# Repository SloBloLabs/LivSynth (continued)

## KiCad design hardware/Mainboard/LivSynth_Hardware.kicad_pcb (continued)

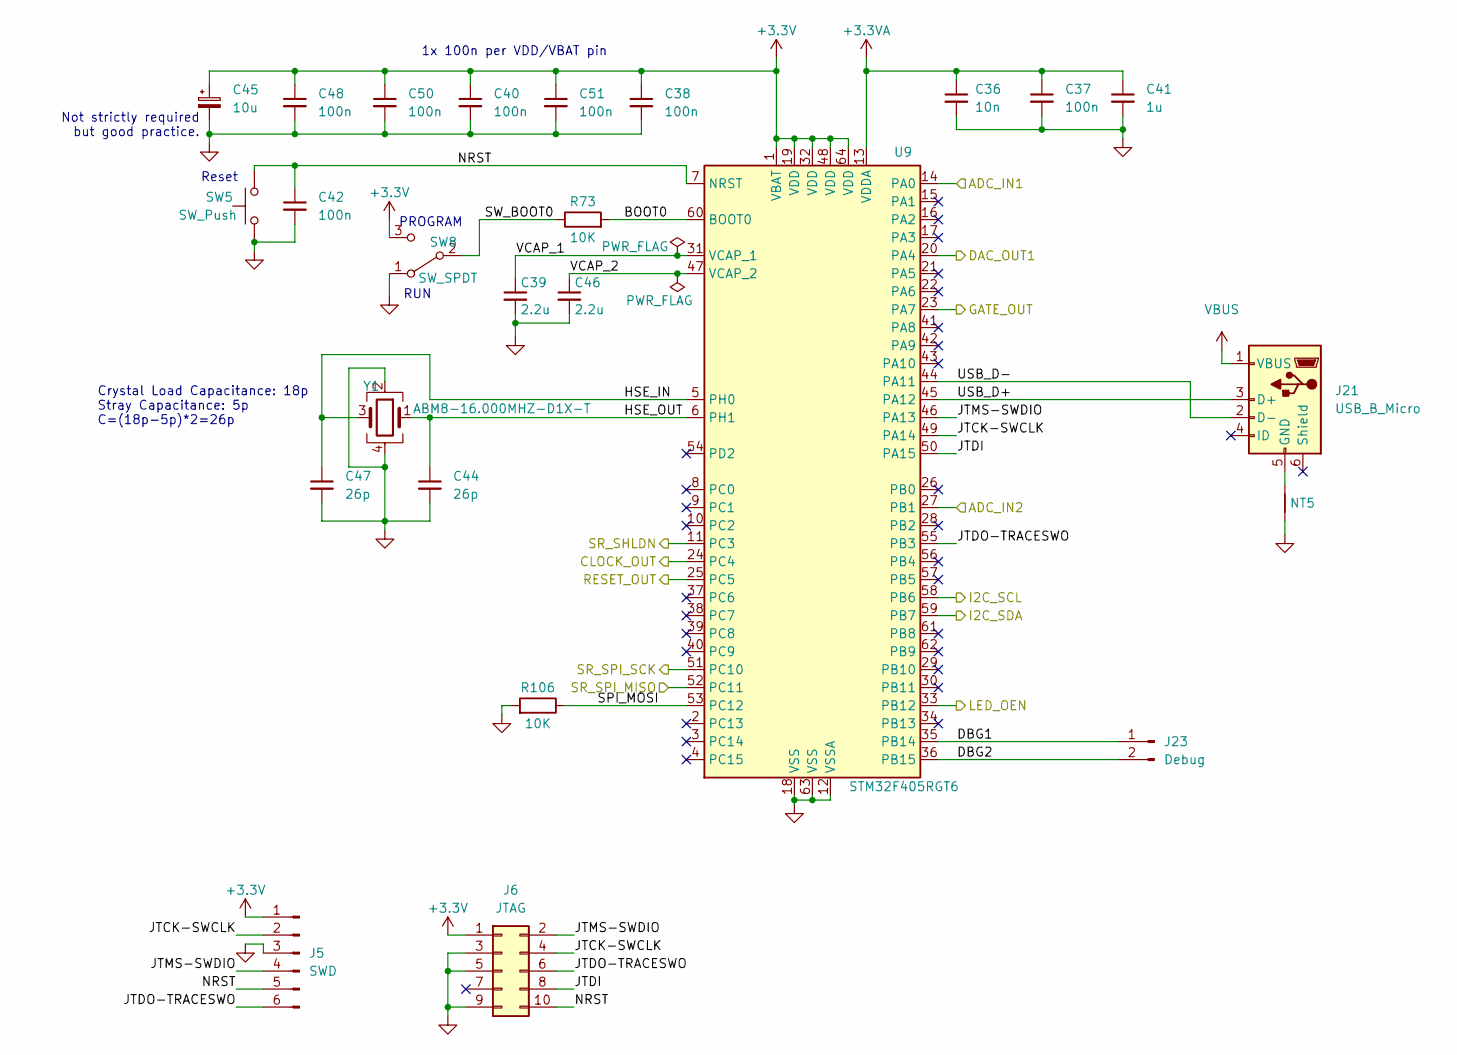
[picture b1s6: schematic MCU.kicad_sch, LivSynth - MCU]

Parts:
C36: 10n; C_Rect_L7.2mm_W2.5mm_P5.00mm_FKS2_FKP2_MKS2_MKP2
C37: 100n; C_Rect_L7.2mm_W2.5mm_P5.00mm_FKS2_FKP2_MKS2_MKP2
C38, C40, C42, C48, C50, C51: 100n; C_0603_1608Metric_Pad1.08x0.95mm_HandSolder; LCSC C282518
C39, C46: 2.2u; C_0603_1608Metric_Pad1.08x0.95mm_HandSolder; LCSC C268016
C41: 1u; C_Rect_L7.2mm_W5.5mm_P5.00mm_FKS2_FKP2_MKS2_MKP2
C44, C47: 26p; C_0603_1608Metric_Pad1.08x0.95mm_HandSolder; LCSC C519484
C45: 10u; CP_Radial_D8.0mm_P3.50mm
J5: SWD; PinHeader_1x06_P2.54mm_Vertical
J6: JTAG; PinHeader_2x05_P1.27mm_Vertical
J21: USB_B_Micro; USB_Micro-B_Wuerth_629105150521
J23: Debug; PinHeader_1x02_P2.54mm_Vertical
NT5: NetTie_2; NetTie-2_SMD_Pad0.5mm
R73, R106: 10K; R_Axial_DIN0207_L6.3mm_D2.5mm_P7.62mm_Horizontal
SW5: SW_Push; SW_SPST_EVQQ2
SW8: SW_SPDT; SW_E-Switch_EG1224_SPDT_Angled
U9: STM32F405RGT6; LQFP-64_10x10mm_P0.5mm; LCSC C15742
Y1: ABM8-16.000MHZ-D1X-T; Crystal_SMD_3225-4Pin_3.2x2.5mm_HandSoldering; LCSC C1985300

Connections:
+3.3V: C38.1, C40.1, C45.1, C48.1, C50.1, C51.1, J5.1, J6.1, SW8.3 (C), U9.1 (VBAT), U9.19 (VDD), U9.32 (VDD), U9.48 (VDD), U9.64 (VDD); also elsewhere on the board
+3.3VA: C36.1, C37.1, C41.1, U9.13 (VDDA); also elsewhere on the board
/EG/GATE_OUT: U9.23 (PA7); also elsewhere on the board
/IO/ADC_IN1: U9.14 (PA0); also elsewhere on the board
/IO/ADC_IN2: U9.27 (PB1); also elsewhere on the board
/IO/CLOCK_OUT: U9.24 (PC4); also elsewhere on the board
/IO/I2C_SCL_IN: U9.58 (PB6); also elsewhere on the board
/IO/I2C_SDA_IN: U9.59 (PB7); also elsewhere on the board
/IO/LED_OEN: U9.33 (PB12); also elsewhere on the board
/IO/RESET_OUT: U9.25 (PC5); also elsewhere on the board
/IO/SR_SHLDN: U9.11 (PC3); also elsewhere on the board
/IO/SR_SPI_CLK: U9.51 (PC10); also elsewhere on the board
/IO/SR_SPI_MISO: U9.52 (PC11); also elsewhere on the board
/MCU/BOOT0: R73.2, U9.60 (BOOT0)
/MCU/DAC_OUT1: U9.20 (PA4); also elsewhere on the board
/MCU/DBG1: J23.1, U9.35 (PB14)
/MCU/DBG2: J23.2, U9.36 (PB15)
/MCU/HSE_IN: C47.1, U9.5 (PH0), Y1.3
/MCU/HSE_OUT: C44.1, U9.6 (PH1), Y1.1
/MCU/JTCK-SWCLK: J5.2, J6.4, U9.49 (PA14)
/MCU/JTDI: J6.8, U9.50 (PA15)
/MCU/JTDO-TRACESWO: J5.6, J6.6, U9.55 (PB3)
/MCU/JTMS-SWDIO: J5.4, J6.2, U9.46 (PA13)
/MCU/NRST: C42.1, J5.5, J6.10, SW5.2, U9.7 (NRST)
/MCU/SPI_MOSI: R106.1, U9.53 (PC12)
/MCU/SW_BOOT0: R73.1, SW8.2 (B)
/MCU/USB_D+: J21.3 (D+), U9.45 (PA12)
/MCU/USB_D-: J21.2 (D-), U9.44 (PA11)
/MCU/VCAP_1: C39.1, U9.31 (VCAP_1)
/MCU/VCAP_2: C46.1, U9.47 (VCAP_2)
GND: C36.2, C37.2, C38.2, C39.2, C40.2, C41.2, C42.2, C44.2, C45.2, C46.2, C47.2, C48.2, C50.2, C51.2, J5.3, J6.3, J6.5, J6.9, NT5.1, R106.2, SW5.1, SW8.1 (A), U9.12 (VSSA), U9.18 (VSS), U9.63 (VSS), Y1.2, Y1.4; also elsewhere on the board
unnamed: J21.5 (GND), NT5.2
VBUS: J21.1 (VBUS); also elsewhere on the board

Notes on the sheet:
Not strictly required but good practice.
RUN
Crystal Load Capacitance: 18p Stray Capacitance: 5p C=(18p-5p)*2=26p
PROGRAM
1x 100n per VDD/VBAT pin
Reset

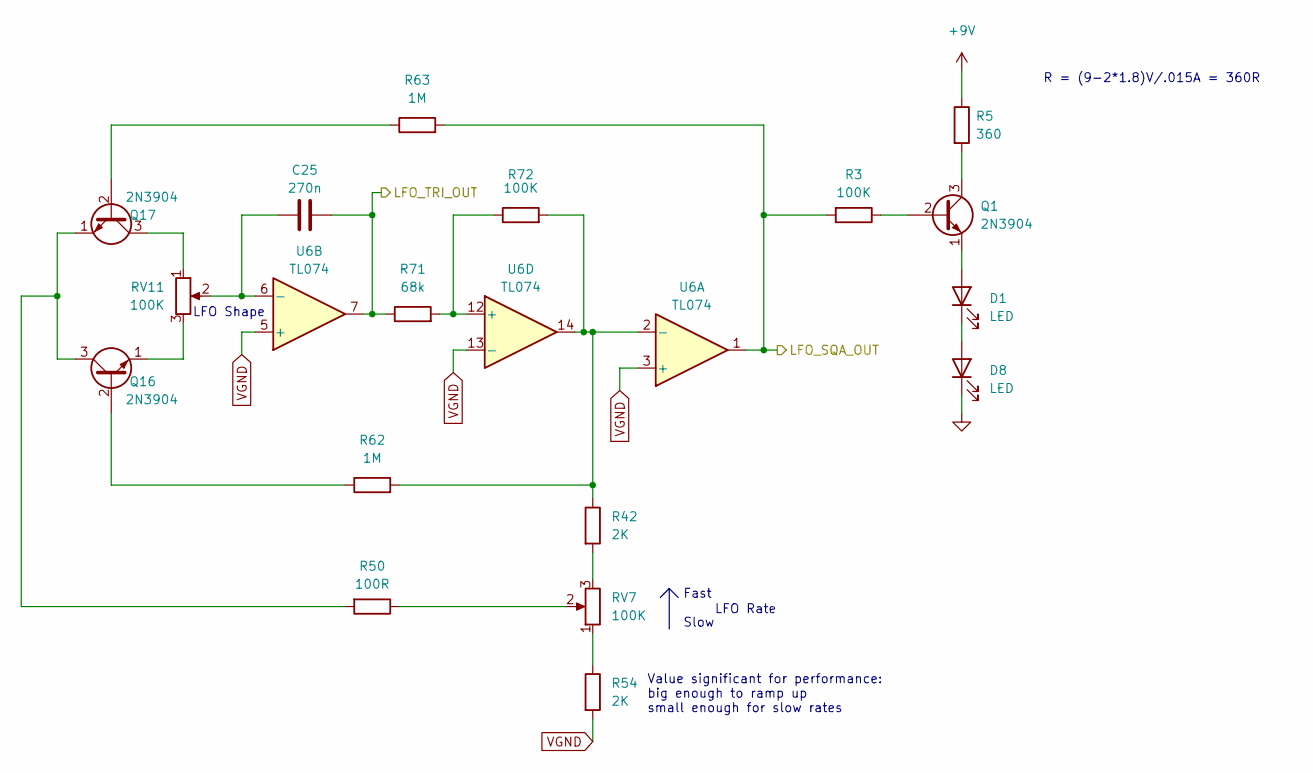
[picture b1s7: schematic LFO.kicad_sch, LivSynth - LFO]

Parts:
C25: 270n; C_Rect_L7.2mm_W5.5mm_P5.00mm_FKS2_FKP2_MKS2_MKP2
D1, D8: LED; LED_D5.0mm
Q1, Q16, Q17: 2N3904; TO-92_Inline
R3, R72: 100K; R_Axial_DIN0207_L6.3mm_D2.5mm_P7.62mm_Horizontal
R5: 360; R_Axial_DIN0207_L6.3mm_D2.5mm_P7.62mm_Horizontal
R42, R54: 2K; R_Axial_DIN0207_L6.3mm_D2.5mm_P7.62mm_Horizontal
R50: 100R; R_Axial_DIN0207_L6.3mm_D2.5mm_P7.62mm_Horizontal
R62, R63: 1M; R_Axial_DIN0207_L6.3mm_D2.5mm_P7.62mm_Horizontal
R71: 68k; R_Axial_DIN0207_L6.3mm_D2.5mm_P7.62mm_Horizontal
RV7, RV11: 100K; RV141F-40-20BL
U6: TL074; SOIC-14_3.9x8.7mm_P1.27mm; LCSC C2057504

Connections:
+9V: R5.1; also elsewhere on the board
/LFO/LFO_SQA_OUT: R3.2, R63.2, U6.1; also elsewhere on the board
/LFO/LFO_TRI_OUT: C25.2, R71.1, U6.7; also elsewhere on the board
GND: D8.1 (K); also elsewhere on the board
unnamed: D1.2 (A), Q1.1 (E)
unnamed: D1.1 (K), D8.2 (A)
unnamed: Q1.2 (B), R3.1
unnamed: Q1.3 (C), R5.2
unnamed: Q16.2 (B), R62.1
unnamed: Q16.3 (C), Q17.1 (E), R50.2
unnamed: Q16.1 (E), RV11.3
unnamed: Q17.2 (B), R63.1
unnamed: Q17.3 (C), RV11.1
unnamed: R42.2, RV7.3
unnamed: R50.1, RV7.2
unnamed: R54.1, RV7.1
unnamed 191: U6.8; also elsewhere on the board
unnamed: R42.1, R62.2, R72.2, U6.2 (-), U6.14
unnamed: C25.1, RV11.2, U6.6 (-)
unnamed 245: U6.10 (+); also elsewhere on the board
unnamed 246: U6.9 (-); also elsewhere on the board
unnamed: R71.2, R72.1, U6.12 (+)
VGND: R54.2, U6.3 (+), U6.5 (+), U6.13 (-); also elsewhere on the board

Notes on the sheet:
LFO Shape
LFO Rate
Fast Slow
R = (9-2*1.8)V/.015A = 360R
Value significant for performance: big enough to ramp up small enough for slow rates

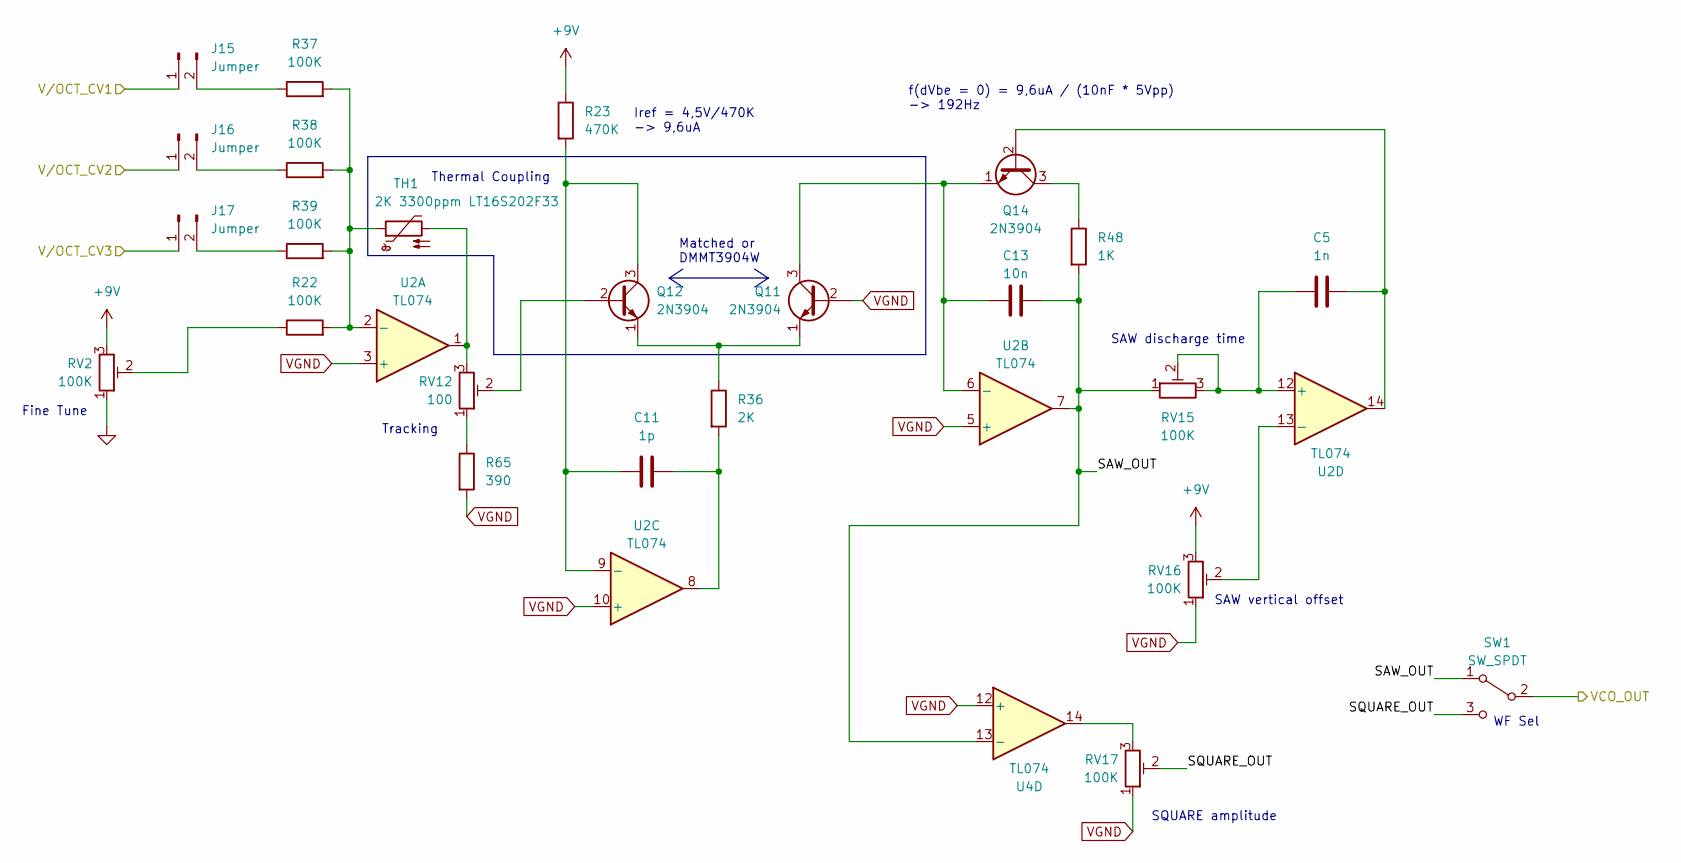
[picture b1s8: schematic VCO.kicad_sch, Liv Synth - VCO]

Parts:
C5: 1n; C_Rect_L7.2mm_W2.5mm_P5.00mm_FKS2_FKP2_MKS2_MKP2
C11: 1p; C_Disc_D3.0mm_W1.6mm_P2.50mm
C13: 10n; C_Rect_L7.2mm_W2.5mm_P5.00mm_FKS2_FKP2_MKS2_MKP2
J15, J16, J17: Jumper; PinHeader_1x02_P2.54mm_Vertical
Q11, Q12, Q14: 2N3904; TO-92_Inline
R22, R37, R38, R39: 100K; R_Axial_DIN0207_L6.3mm_D2.5mm_P7.62mm_Horizontal
R23: 470K; R_Axial_DIN0207_L6.3mm_D2.5mm_P7.62mm_Horizontal
R36: 2K; R_Axial_DIN0207_L6.3mm_D2.5mm_P7.62mm_Horizontal
R48: 1K; R_Axial_DIN0207_L6.3mm_D2.5mm_P7.62mm_Horizontal
R65: 390; R_Axial_DIN0207_L6.3mm_D2.5mm_P7.62mm_Horizontal
RV2, RV15, RV16, RV17: 100K; Potentiometer_Bourns_3296W_Vertical
RV12: 100; Potentiometer_Bourns_3296W_Vertical
SW1: SW_SPDT; SW_Toggle_MS500
TH1: 2K 3300ppm LT16S202F33; R_Axial_DIN0207_L6.3mm_D2.5mm_P7.62mm_Horizontal
U2, U4: TL074; SOIC-14_3.9x8.7mm_P1.27mm; LCSC C2057504

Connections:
+9V: R23.1, RV2.3, RV16.3; also elsewhere on the board
/ModMatrix/VCF_EG_OUT: U4.1; also elsewhere on the board
/ModMatrix/VCO_EG_OUT: J17.1, U4.7; also elsewhere on the board
/ModMatrix/VCO_LFO_OUT: J16.1; also elsewhere on the board
/Slew/V/OCT_OUT: J15.1, U4.8, U4.9 (-)
/VCF/VCF_IN: SW1.2 (B); also elsewhere on the board
/VCO/SAW_OUT: C13.2, R48.2, RV15.1, SW1.1 (A), U2.7, U4.13 (-)
/VCO/SQUARE_OUT: RV17.2, SW1.3 (C)
GND: RV2.1; also elsewhere on the board
unnamed: C11.2, R36.2, U2.8
unnamed: J15.2, R37.1
unnamed: J16.2, R38.1
unnamed: J17.2, R39.1
unnamed: C13.1, Q11.3 (C), Q14.1 (E), U2.6 (-)
unnamed: Q11.1 (E), Q12.1 (E), R36.1
unnamed: Q12.2 (B), RV12.2
unnamed: C11.1, Q12.3 (C), R23.2, U2.9 (-)
unnamed: C5.2, Q14.2 (B), U2.14
unnamed: Q14.3 (C), R48.1
unnamed: R22.1, RV2.2
unnamed: R65.1, RV12.1
unnamed: RV12.3, TH1.2, U2.1
unnamed: RV17.3, U4.14
unnamed: R22.2, R37.2, R38.2, R39.2, TH1.1, U2.2 (-)
unnamed: C5.1, RV15.2, RV15.3, U2.12 (+)
unnamed: RV16.2, U2.13 (-)
unnamed 235: U4.3 (+); also elsewhere on the board
unnamed 236: U4.2 (-); also elsewhere on the board
unnamed 237: U4.5 (+); also elsewhere on the board
unnamed 238: U4.6 (-); also elsewhere on the board
unnamed 239: U4.10 (+); also elsewhere on the board
VGND: Q11.2 (B), R65.2, RV16.1, RV17.1, U2.3 (+), U2.5 (+), U2.10 (+), U4.12 (+); also elsewhere on the board

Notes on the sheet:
f(dVbe = 0) = 9,6uA / (10nF * 5Vpp) -> 192Hz
WF Sel
SAW discharge time
Iref = 4,5V/470K -> 9,6uA
Tracking
Matched or DMMT3904W
SQUARE amplitude
Thermal Coupling
Fine Tune
SAW vertical offset

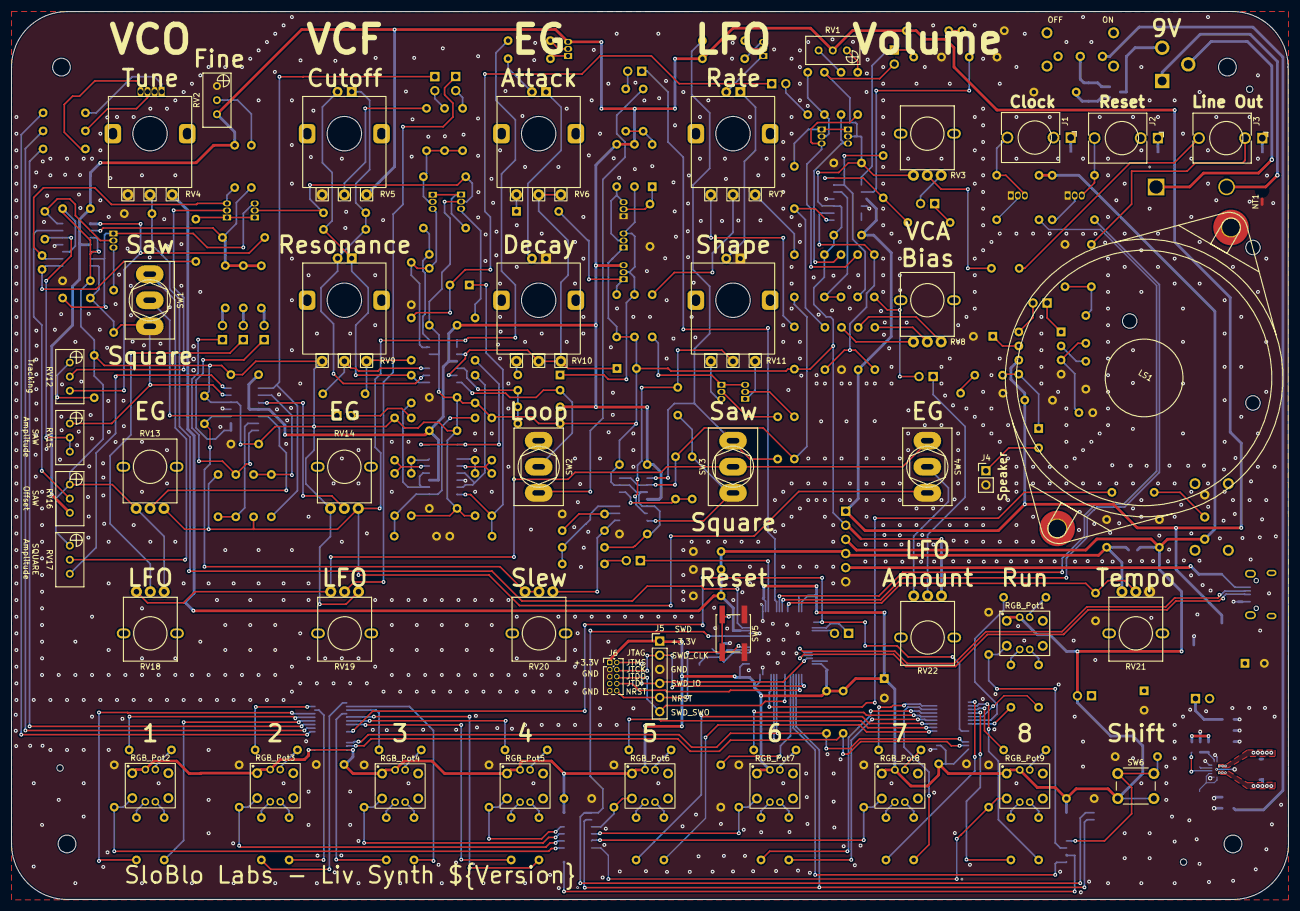
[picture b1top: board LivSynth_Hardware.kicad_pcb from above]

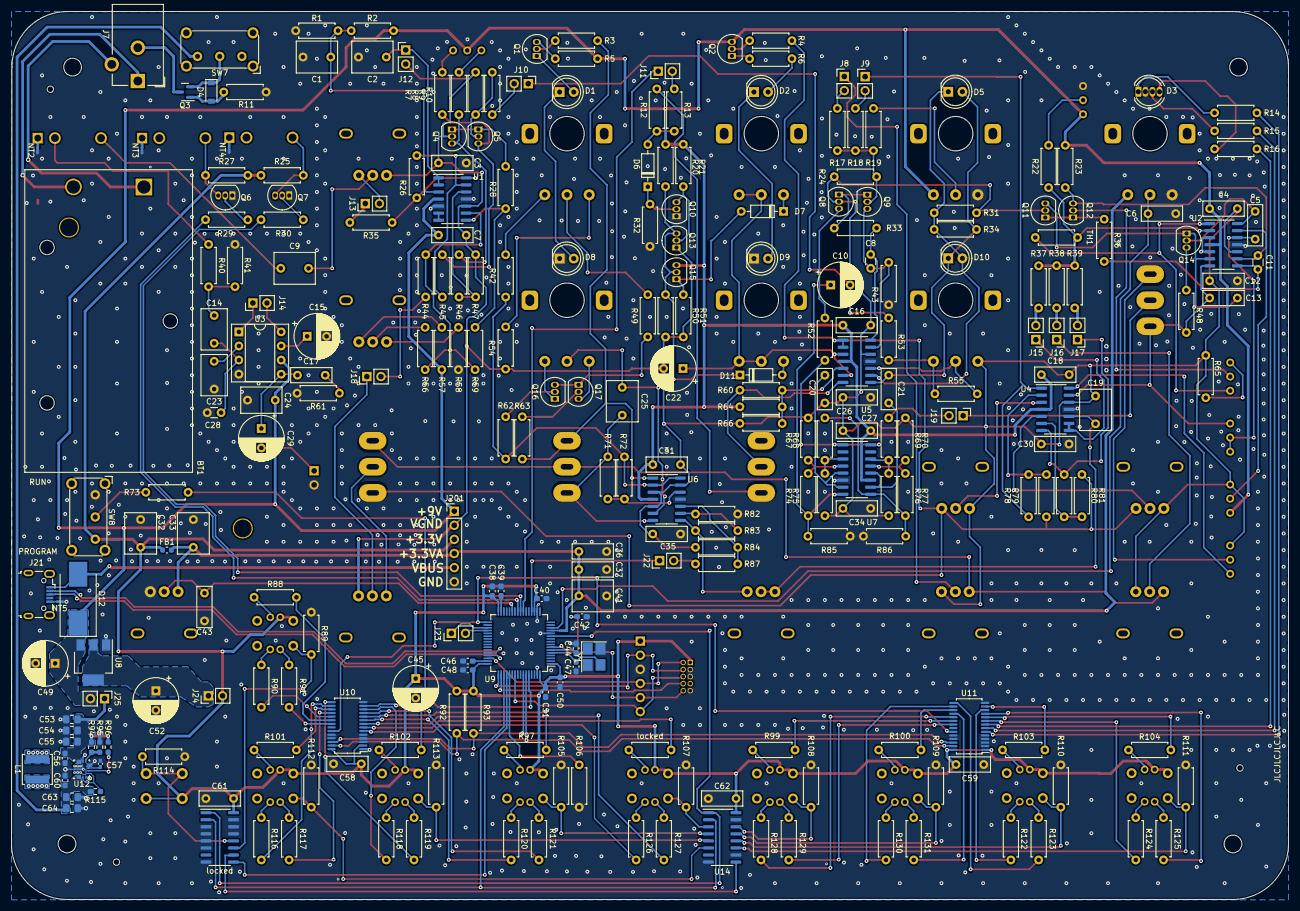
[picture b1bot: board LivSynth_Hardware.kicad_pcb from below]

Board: 2 copper layers, 230.0 x 159.9 mm, 320 parts (268 on the bottom side), 254 nets.

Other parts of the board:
C19: 1u; C_Rect_L7.2mm_W5.5mm_P5.00mm_FKS2_FKP2_MKS2_MKP2
J10, J18, J22: Jumper; PinHeader_1x02_P2.54mm_Vertical
Q4, Q5: 2N3904; TO-92_Inline
R7, R9: 20K; R_Axial_DIN0207_L6.3mm_D2.5mm_P7.62mm_Horizontal
R8: 390; R_Axial_DIN0207_L6.3mm_D2.5mm_P7.62mm_Horizontal
R10, R26, R47, R56, R78, R79, R80, R81, R82, R83, R87: 100K; R_Axial_DIN0207_L6.3mm_D2.5mm_P7.62mm_Horizontal
R28: 4K7; R_Axial_DIN0207_L6.3mm_D2.5mm_P7.62mm_Horizontal
R35, R45, R46: 1K; R_Axial_DIN0207_L6.3mm_D2.5mm_P7.62mm_Horizontal
R44: 68K; R_Axial_DIN0207_L6.3mm_D2.5mm_P7.62mm_Horizontal
R57: 24K; R_Axial_DIN0207_L6.3mm_D2.5mm_P7.62mm_Horizontal
R58: 150K; R_Axial_DIN0207_L6.3mm_D2.5mm_P7.62mm_Horizontal
R59: 47K; R_Axial_DIN0207_L6.3mm_D2.5mm_P7.62mm_Horizontal
R84: 330K; R_Axial_DIN0207_L6.3mm_D2.5mm_P7.62mm_Horizontal
RV1: 1K; Potentiometer_Bourns_3296W_Vertical
RV8, RV13, RV14, RV18, RV19, RV20, RV22: 100K; Alpha_RD901F
SW3, SW4: SW_SPDT; SW_Toggle_MS500
locked: 220; R_Axial_DIN0207_L6.3mm_D2.5mm_P7.62mm_Horizontal
locked#2: 74HC165; SOIC-16_3.9x9.9mm_P1.27mm

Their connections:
+3.3V: locked#2.16 (VCC); also elsewhere on the board
+9V: R57.1, RV1.2; also elsewhere on the board
/EG/AR_OUT: R79.1, R81.1, RV13.3, RV14.3, SW4.1 (A); also elsewhere on the board
/IO/BTN9: locked#2.11 (D0); also elsewhere on the board
/IO/BTN_SHIFT: locked#2.12 (D1); also elsewhere on the board
/IO/P5_G: locked.2; also elsewhere on the board
/IO/SR_SHLDN: locked#2.1 (~PL); also elsewhere on the board
/IO/SR_SPI_CLK: locked#2.2 (CP); also elsewhere on the board
/IO/SR_SPI_MISO: locked#2.9 (Q7); also elsewhere on the board
/IO/VCA_IN: R35.2; also elsewhere on the board
/LFO/LFO_SQA_OUT: SW3.1 (A); also elsewhere on the board
/LFO/LFO_TRI_OUT: SW3.3 (C); also elsewhere on the board
/MCU/DAC_OUT1: J22.1; also elsewhere on the board
/ModMatrix/VCA_CV_OUT: J18.1, RV22.2
/ModMatrix/VCF_EG_OUT: R78.2; also elsewhere on the board
/ModMatrix/VCF_LFO_OUT: RV19.2; also elsewhere on the board
/ModMatrix/VCO_EG_OUT: R80.2; also elsewhere on the board
/ModMatrix/VCO_LFO_OUT: RV18.2; also elsewhere on the board
/VCA/VCA_IN: J10.1; also elsewhere on the board
GND: R58.2, R82.1, locked#2.3 (D4), locked#2.4 (D5), locked#2.5 (D6), locked#2.6 (D7), locked#2.8 (GND), locked#2.13 (D2), locked#2.14 (D3), locked#2.15 (~CE); also elsewhere on the board
unnamed: J10.2, R10.1
unnamed: J18.2, R44.1
unnamed: J22.2, R87.1
unnamed: Q4.2 (B), R8.1, R10.2
unnamed: Q4.3 (C), R7.2, R45.1
unnamed: Q4.1 (E), Q5.1 (E), R28.1
unnamed: Q5.3 (C), R9.2, R46.1
unnamed: R7.1, RV1.1
unnamed: R9.1, RV1.3
unnamed 179: R26.1, R35.1; also elsewhere on the board
unnamed 180: R28.2, R59.2; also elsewhere on the board
unnamed: R56.1, RV8.2
unnamed: R57.2, RV8.3
unnamed: R58.1, RV8.1
unnamed 191: R83.2, RV20.1; also elsewhere on the board
unnamed 208: locked.1; also elsewhere on the board
unnamed: RV18.3, RV19.3, SW3.2 (B), SW4.3 (C)
unnamed: RV22.3, SW4.2 (B)
unnamed 226: R44.2, R56.2, R59.1; also elsewhere on the board
unnamed 227: R46.2, R47.2; also elsewhere on the board
unnamed 228: R26.2, R45.2; also elsewhere on the board
unnamed 235: RV14.2; also elsewhere on the board
unnamed 236: R78.1, R79.2; also elsewhere on the board
unnamed 237: RV13.2; also elsewhere on the board
unnamed 238: R80.1, R81.2; also elsewhere on the board
unnamed 239: C19.1, RV20.2, RV20.3; also elsewhere on the board
unnamed 245: R84.2, R87.2; also elsewhere on the board
unnamed 246: R82.2, R83.1; also elsewhere on the board
unnamed 253: locked#2.10 (DS); also elsewhere on the board
VGND: C19.2, Q5.2 (B), R8.2, R47.1, R84.1, RV13.1, RV14.1, RV18.1, RV19.1, RV22.1; also elsewhere on the board

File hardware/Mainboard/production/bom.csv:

Designator,Footprint,Quantity,Value,LCSC Part #
BT1,BatteryHolder_Eagle_12BH611-GR,1,9V,
"C1, C19, C2, C25, C32, C33, C41, C9",C_Rect_L7.2mm_W5.5mm_P5.00mm_FKS2_FKP2_MKS2_MKP2,8,1u,
C10,CP_Radial_D8.0mm_P3.50mm,1,33u,
"C11, C8",C_Disc_D3.0mm_W1.6mm_P2.50mm,2,1p,
"C12, C13, C16, C17, C18, C26, C27, C3, C30, C31, C34, C35, C37, C4, C43, C58, C59, C6, C61, C62, C7",C_Rect_L7.2mm_W2.5mm_P5.00mm_FKS2_FKP2_MKS2_MKP2,21,100n,
"C14, C23, C24",C_Rect_L7.2mm_W4.5mm_P5.00mm_FKS2_FKP2_MKS2_MKP2,3,270n,
"C15, C22, C45, C49",CP_Radial_D8.0mm_P3.50mm,4,10u,
"C20, C5",C_Rect_L7.2mm_W2.5mm_P5.00mm_FKS2_FKP2_MKS2_MKP2,2,1n,
"C21, C36",C_Rect_L7.2mm_W2.5mm_P5.00mm_FKS2_FKP2_MKS2_MKP2,2,10n,
C28,C_Disc_D3.0mm_W1.6mm_P2.50mm,1,47p,
C29,CP_Radial_D8.0mm_P3.50mm,1,470u,
"C38, C40, C42, C48, C50, C51",C_0603_1608Metric_Pad1.08x0.95mm_HandSolder,6,100n,C282518
"C39, C46",C_0603_1608Metric_Pad1.08x0.95mm_HandSolder,2,2.2u,C268016
"C44, C47",C_0603_1608Metric_Pad1.08x0.95mm_HandSolder,2,26p,C519484
C52,CP_Radial_D8.0mm_P3.50mm,1,22u,
"C53, C54, C55",C_0805_2012Metric_Pad1.18x1.45mm_HandSolder,3,22u,C415296
"C56, C60",C_0603_1608Metric_Pad1.08x0.95mm_HandSolder,2,10u, C96446
C57,C_0402_1005Metric_Pad0.74x0.62mm_HandSolder,1,100n, C1523
"C63, C64",C_0805_2012Metric_Pad1.18x1.45mm_HandSolder,2,10u, C109040
"D1, D10, D2, D5, D8, D9",LED_D5.0mm,6,LED,
"D11, D6, D7",D_DO-35_SOD27_P7.62mm_Horizontal,3,1N4148,
D12,D_SMC_Handsoldering,1,SS310,
D3,LED_D5.0mm-4_RGB,1,LED_RKGB,
D4,D_SOD-123,1,8V2, C438308
FB1,L_0603_1608Metric,1,120R@100MHz,
"H1, H2, H5, H6",MountingHole_3.2mm_M3,4,MountingHole,
"J1, J2, J3",Thonkiconn_PJ398SM,3,PJ398SM,
"J10, J11, J13, J14, J15, J16, J17, J18, J19, J22, J8, J9",PinHeader_1x02_P2.54mm_Vertical,12,Jumper,
J12,PinHeader_1x02_P2.54mm_Vertical,1,VGND,
J201,PinHeader_1x06_P2.54mm_Vertical,1,Test Points,
J21,USB_Micro-B_Wuerth_629105150521,1,USB_B_Micro,
J23,PinHeader_1x02_P2.54mm_Vertical,1,Debug,
J24,PinHeader_1x02_P2.54mm_Vertical,1,3V3,
J25,PinHeader_1x02_P2.54mm_Vertical,1,9V,
J4,PinHeader_1x02_P2.54mm_Vertical,1,IDC,
J5,PinHeader_1x06_P2.54mm_Vertical,1,SWD,
J6,PinHeader_2x05_P1.27mm_Vertical,1,JTAG,
J7,BarrelJack_CUI_PJ-102AH_Horizontal,1,Barrel_Jack_Switch,
L1,L_Sunlord_SWPA5020S,1,1u5,C279945
LS1,LSM-50M NO-B,1,LSM-50M/NO-B 8R (<32R) 1W,
"Q1, Q10, Q11, Q12, Q13, Q14, Q15, Q16, Q17, Q2, Q4, Q5, Q6, Q7",TO-92_Inline,14,2N3904,
Q3,SOT-23,1,AO3401A,C347476
"Q8, Q9",TO-92_Inline,2,2N3906,
"R1, R10, R11, R12, R13, R19, R2, R21, R22, R26, R3, R32, R37, R38, R39, R4, R40, R44, R47, R51, R56, R64, R66, R72, R78, R79, R80, R81, R82, R83, R87",R_Axial_DIN0207_L6.3mm_D2.5mm_P7.62mm_Horizontal,31,100K,
"R100, R101, R102, R103, R104, R117, R119, R121, R123, R125, R127, R129, R131, R14, R88, R91, R97, R98, R99",R_Axial_DIN0207_L6.3mm_D2.5mm_P7.62mm_Horizontal,19,220R,
"R105, R106, R107, R108, R109, R110, R111, R112, R113, R114, R29, R30, R34, R68, R69, R73, R89",R_Axial_DIN0207_L6.3mm_D2.5mm_P7.62mm_Horizontal,17,10K,
R115,R_0603_1608Metric_Pad0.98x0.95mm_HandSolder,1,10K, C25804
"R116, R118, R120, R122, R124, R126, R128, R130, R90",R_Axial_DIN0207_L6.3mm_D2.5mm_P7.62mm_Horizontal,9,470R,
"R15, R16, R25, R27, R35, R45, R46, R48",R_Axial_DIN0207_L6.3mm_D2.5mm_P7.62mm_Horizontal,8,1K,
"R17, R18, R59",R_Axial_DIN0207_L6.3mm_D2.5mm_P7.62mm_Horizontal,3,47K,
"R20, R60",R_Axial_DIN0207_L6.3mm_D2.5mm_P7.62mm_Horizontal,2,82K,
"R23, R7, R9",R_Axial_DIN0207_L6.3mm_D2.5mm_P7.62mm_Horizontal,3,20K,
"R24, R31, R33, R36, R42, R54",R_Axial_DIN0207_L6.3mm_D2.5mm_P7.62mm_Horizontal,6,2K,
"R28, R52, R74, R77, R92, R93",R_Axial_DIN0207_L6.3mm_D2.5mm_P7.62mm_Horizontal,6,4K7,
R41,R_Axial_DIN0207_L6.3mm_D2.5mm_P7.62mm_Horizontal,1,6K2,
R43,R_Axial_DIN0207_L6.3mm_D2.5mm_P7.62mm_Horizontal,1,470K,
R49,R_Axial_DIN0207_L6.3mm_D2.5mm_P7.62mm_Horizontal,1,820K,
"R5, R6",R_Axial_DIN0207_L6.3mm_D2.5mm_P7.62mm_Horizontal,2,360,
R50,R_Axial_DIN0207_L6.3mm_D2.5mm_P7.62mm_Horizontal,1,100R,
R53,R_Axial_DIN0207_L6.3mm_D2.5mm_P7.62mm_Horizontal,1,8K2,
R55,R_Axial_DIN0207_L6.3mm_D2.5mm_P7.62mm_Horizontal,1,2K2,
R57,R_Axial_DIN0207_L6.3mm_D2.5mm_P7.62mm_Horizontal,1,24K,
R58,R_Axial_DIN0207_L6.3mm_D2.5mm_P7.62mm_Horizontal,1,150K,
R61,R_Axial_DIN0207_L6.3mm_D2.5mm_P7.62mm_Horizontal,1,10R,
"R62, R63",R_Axial_DIN0207_L6.3mm_D2.5mm_P7.62mm_Horizontal,2,1M,
"R65, R8",R_Axial_DIN0207_L6.3mm_D2.5mm_P7.62mm_Horizontal,2,390,
"R67, R70, R75, R76",R_Axial_DIN0207_L6.3mm_D2.5mm_P7.62mm_Horizontal,4,100,
R71,R_Axial_DIN0207_L6.3mm_D2.5mm_P7.62mm_Horizontal,1,51K,
R84,R_Axial_DIN0207_L6.3mm_D2.5mm_P7.62mm_Horizontal,1,330K,
"R85, R86",R_Axial_DIN0207_L6.3mm_D2.5mm_P7.62mm_Horizontal,2,2K7,
R94,R_0603_1608Metric_Pad0.98x0.95mm_HandSolder,1,402K, C844562
R95,R_0603_1608Metric_Pad0.98x0.95mm_HandSolder,1,39K, C163424
R96,R_0603_1608Metric_Pad0.98x0.95mm_HandSolder,1,100K,
"RGB_Pot1, RGB_Pot2, RGB_Pot3, RGB_Pot4, RGB_Pot5, RGB_Pot6, RGB_Pot7, RGB_Pot8, RGB_Pot9",TC002-N11AS2XT-RGB,9,TC002-N11AS2XT-RGB,
RV1,Potentiometer_Bourns_3296W_Vertical,1,1K,
"RV10, RV11, RV5, RV6, RV7",RV141F-40-20BL,5,100K,
"RV12, RV2",Potentiometer_Bourns_3296W_Vertical,2,100,
"RV13, RV14, RV18, RV19, RV20, RV22, RV3, RV8",Alpha_RD901F,8,100K,
"RV15, RV16, RV17",Potentiometer_Bourns_3296W_Vertical,3,100K,
RV21,Alpha_RD901F,1,10K,
"RV4, RV9",RV141F-40-20BL,2,10K,
"SW1, SW3, SW4",SW_Toggle_MS500C,3,SW_SPDT,
SW2,SW_Toggle_MS500C,1,SW_SPST,
SW5,SW_SPST_EVQQ2,1,SW_Push,
SW6,E-Switch_TL1105SP,1,SW_Push,
"SW7, SW8",SW_E-Switch_EG1224_SPDT_Angled,2,SW_SPDT,
TH1,R_Axial_DIN0207_L6.3mm_D2.5mm_P7.62mm_Horizontal,1,2K 3300ppm LT16S202F33,
"U1, U2, U4, U5, U6",SOIC-14_3.9x8.7mm_P1.27mm,5,TL074,C2057504
"U10, U11",TSSOP-28_4.4x9.7mm_P0.65mm,2,PCA9685PW,C2678753
U12,TPS63070x,1,TPS63070,C109322
"U13, U14",SOIC-16_3.9x9.9mm_P1.27mm,2,74HC165,C7334
U3,DIP-8_W7.62mm_Socket,1,LM386,
U7,SOP-16_3.9x9.9mm_P1.27mm,1,LM13700,C4370932
U8,SOT-223-3_TabPin2,1,LM1117-3.3,C126027
U9,LQFP-64_10x10mm_P0.5mm,1,STM32F405RGT6,C15742
Y1,Crystal_SMD_3225-4Pin_3.2x2.5mm_HandSoldering,1,ABM8-16.000MHZ-D1X-T,C1985300

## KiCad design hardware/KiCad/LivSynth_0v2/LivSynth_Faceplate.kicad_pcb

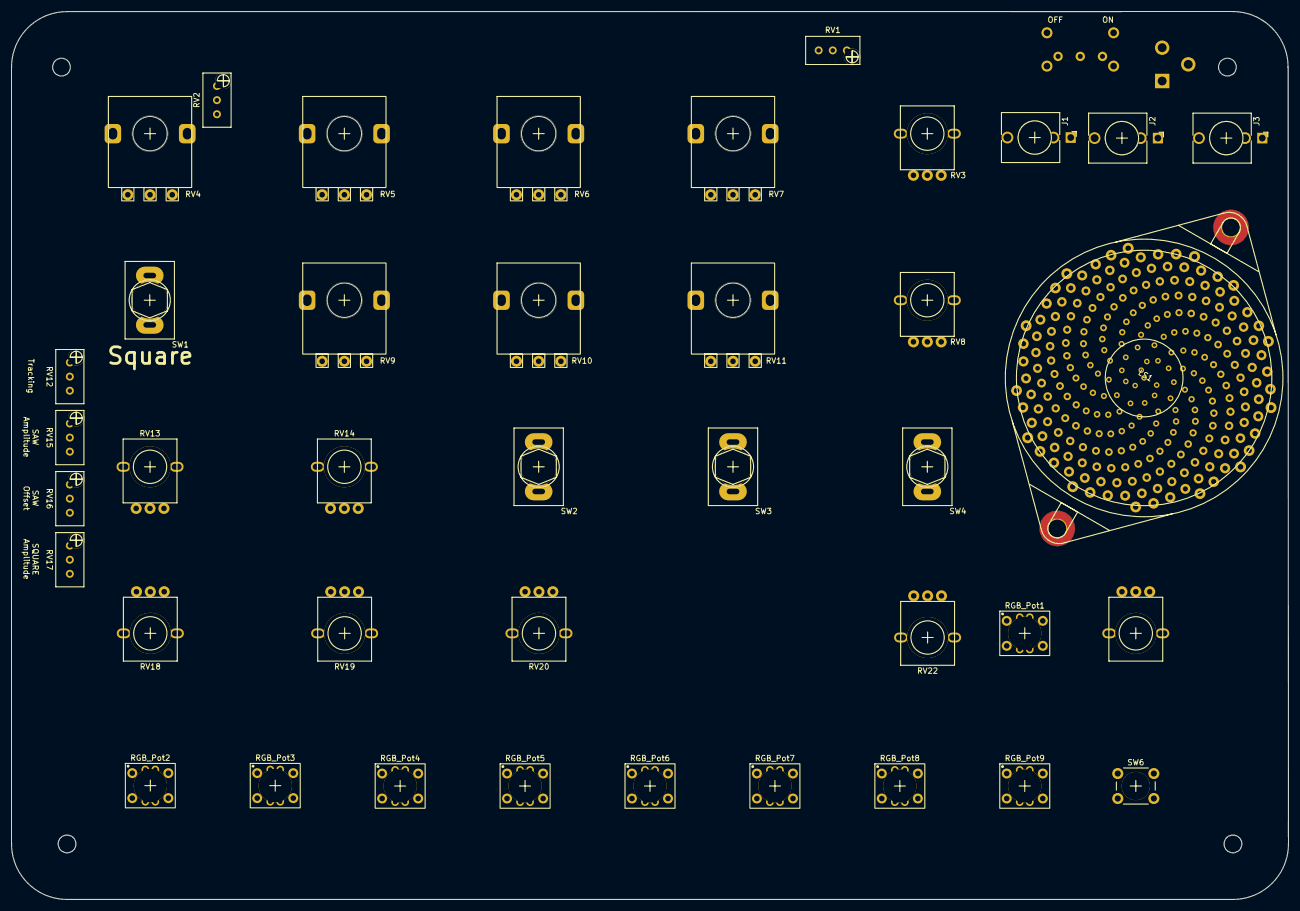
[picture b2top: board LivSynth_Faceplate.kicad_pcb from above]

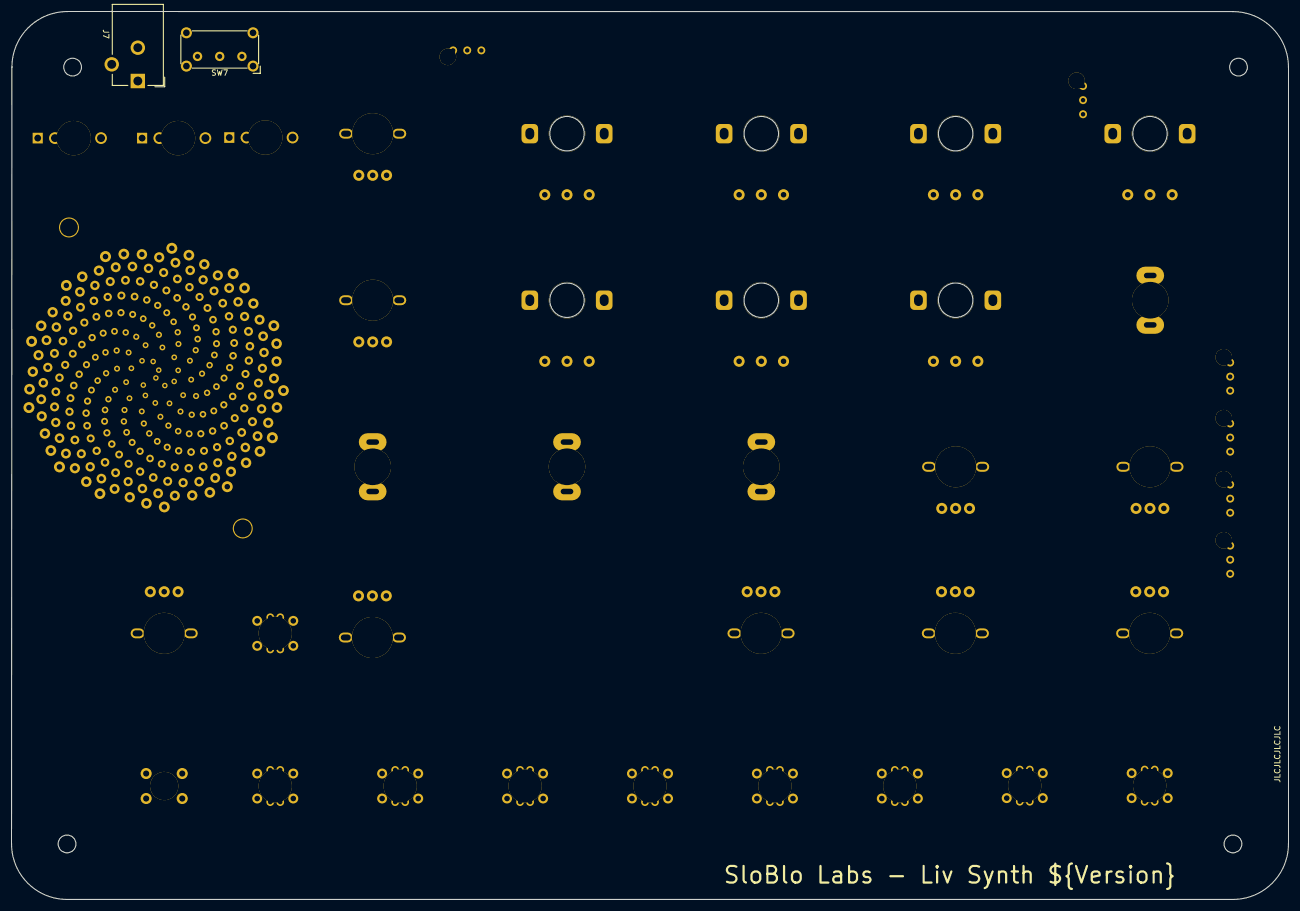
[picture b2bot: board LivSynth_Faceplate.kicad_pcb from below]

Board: 2 copper layers, 230.0 x 159.9 mm, 46 parts (2 on the bottom side), 13 nets, no tracks yet.

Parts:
H1, H2, H5, H6: MountingHole; MountingHole_3.2mm_M3
J1, J2, J3: PJ398SM; Thonkiconn_PJ398SM
J7: Barrel_Jack_Switch; BarrelJack_CUI_PJ-102AH_Horizontal
LS1: LSM-50M/NO-B 8R (<32R) 1W; LSM-50M NO-B
RGB_Pot1, RGB_Pot2, RGB_Pot3, RGB_Pot4, RGB_Pot5, RGB_Pot6, RGB_Pot7, RGB_Pot8, RGB_Pot9: TC002-N11AS2XT-RGB
RV1: 1K; Potentiometer_Bourns_3296W_Vertical
RV2, RV12: 100; Potentiometer_Bourns_3296W_Vertical
RV3, RV8, RV13, RV14, RV18, RV19, RV20, RV22: 100K; Alpha_RD901F
RV4, RV9: 10K; RV141F-40-20BL
RV5, RV6, RV7, RV10: 100K; RV141F-40-20BL
RV11: 100k; RV141F-40-20BL
RV15, RV16, RV17: 100K; Potentiometer_Bourns_3296W_Vertical
RV21: 10K; Alpha_RD901F
SW1, SW3, SW4: SW_SPDT; SW_Toggle_MS500C
SW2: SW_SPST; SW_Toggle_MS500C
SW6: SW_Push; E-Switch_TL1105SP
SW7: SW_SPDT; SW_E-Switch_EG1224_SPDT_Angled

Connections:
+3.3V: RGB_Pot1.1 (UP-A), RGB_Pot1.5 (CA), RGB_Pot2.1 (UP-A), RGB_Pot2.5 (CA), RGB_Pot3.1 (UP-A), RGB_Pot3.5 (CA), RGB_Pot4.1 (UP-A), RGB_Pot4.5 (CA), RGB_Pot5.1 (UP-A), RGB_Pot5.5 (CA), RGB_Pot6.1 (UP-A), RGB_Pot6.5 (CA), RGB_Pot7.1 (UP-A), RGB_Pot7.5 (CA), RGB_Pot8.1 (UP-A), RGB_Pot8.5 (CA), RGB_Pot9.1 (UP-A), RGB_Pot9.5 (CA), SW6.2
+3.3VA: RV4.3, RV21.3
+9V: RV1.2, RV2.3, RV5.3, RV16.3
/EG/AR_OUT: RV13.3, RV14.3, SW4.1 (A)
/VCO/SAW_OUT: RV15.1, SW1.1 (A)
/VCO/SQUARE_OUT: RV17.2, SW1.3 (C)
GND: RV2.1, RV4.1, RV5.1, RV21.1
unnamed: RV15.2, RV15.3
unnamed: RV20.2, RV20.3
unnamed: RV6.2, RV6.3, RV10.2, RV10.3
unnamed: RV18.3, RV19.3, SW3.+ (B), SW4.3 (C)
unnamed: RV22.3, SW4.+ (B)
VGND: RV3.1, RV9.1, RV13.1, RV14.1, RV16.1, RV17.1, RV18.1, RV19.1, RV22.1

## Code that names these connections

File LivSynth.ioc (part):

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Mcu.Name=STM32F405RGTx
Mcu.Package=LQFP64
Mcu.UserName=STM32F405RGTx
PA0-WKUP.GPIOParameters=GPIO_Label
PA0-WKUP.GPIO_Label=ADC_IN1
PA0-WKUP.Signal=ADCx_IN0
PA11.Mode=Device_Only
PA11.Signal=USB_OTG_FS_DM
PA12.Mode=Device_Only
PA12.Signal=USB_OTG_FS_DP
PA13.Mode=Trace_Asynchronous_SW
PA13.Signal=SYS_JTMS-SWDIO
PA14.Mode=Trace_Asynchronous_SW
PA14.Signal=SYS_JTCK-SWCLK
PA4.Signal=COMP_DAC1_group
PA7.GPIOParameters=GPIO_Label
PA7.GPIO_Label=GATE_OUT
PA7.Signal=GPIO_Output
PB1.GPIOParameters=GPIO_Label
PB1.GPIO_Label=ADC_IN2
PB1.Signal=ADCx_IN9
PB12.GPIOParameters=GPIO_Label
PB12.GPIO_Label=LED_OEN
PB12.Signal=GPIO_Output
PB14.GPIOParameters=GPIO_Label
PB14.GPIO_Label=DBG1
PB14.Signal=GPIO_Output
PB15.GPIOParameters=GPIO_Label
PB15.GPIO_Label=DBG2
PB15.Signal=GPIO_Output
PB3.Mode=Trace_Asynchronous_SW
PB3.Signal=SYS_JTDO-SWO
PB6.Mode=I2C
PB6.Signal=I2C1_SCL
PB7.Mode=I2C
PB7.Signal=I2C1_SDA
PC10.GPIOParameters=GPIO_Label
PC10.GPIO_Label=SPI_SCK
PC10.Mode=Full_Duplex_Master
PC10.Signal=SPI3_SCK
PC11.GPIOParameters=GPIO_Label
PC11.GPIO_Label=SPI_MISO
PC11.Mode=Full_Duplex_Master
PC11.Signal=SPI3_MISO
PC12.GPIOParameters=GPIO_Label
PC12.GPIO_Label=SPI_MOSI
PC12.Mode=Full_Duplex_Master
PC12.Signal=SPI3_MOSI
PC3.GPIOParameters=GPIO_Label
PC3.GPIO_Label=SR_SHLDN
PC3.Signal=GPIO_Output
PC4.GPIOParameters=GPIO_Label
PC4.GPIO_Label=CLOCK_OUT
PC4.Signal=GPIO_Output
PC5.GPIOParameters=GPIO_Label
PC5.GPIO_Label=RESET_OUT
PC5.Signal=GPIO_Output
PH0-OSC_IN.Mode=HSE-External-Oscillator
PH0-OSC_IN.Signal=RCC_OSC_IN
PH1-OSC_OUT.Mode=HSE-External-Oscillator
PH1-OSC_OUT.Signal=RCC_OSC_OUT
RCC.HSE_VALUE=16000000
RCC.SYSCLKFreq_VALUE=168000000
RCC.SYSCLKSource=RCC_SYSCLKSOURCE_PLLCLK
board=custom

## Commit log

2022-07-30 initial upload
2022-07-30 Fill all title blocks
2022-09-04 Initial Routing finished
2022-09-09 Rework for polyester film capacitors
2022-09-09 Silkscreen cosmetics
2022-09-09 Additional Silkscreen Cosmetics
2022-09-13 Change LED status circuits
2022-09-14 White balance for RGB LEDs
2022-09-14 White balance for RGB LEDs (update comments)
2022-09-19 Adjust crystal cap values Add BOM csv
2022-09-24 Use correct Elko sizes (8mm/3.5mm)
2022-09-30 0v1 Ready for Production
2022-11-13 Start Testing the prototype
2022-11-13 Add sources from LivSynth_Nucleo and fix the build
2022-11-20 LEDs working DFU connection from HS to FS
2022-11-20 Compatibility for STM32CubeIDE
2022-11-24 ButtonMatrix working debug launch configuration added shift register moved to full-duplex mode (simplex does not support triggering the latch line and puts too much stress on the operation) Hardware 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
2022-11-24 ADC working ITM Debug print working
2022-11-24 Dac output working
2022-11-24 dio working (fixing inversion bug in button matrix processor)
2022-11-25 Sequencer engine working
2022-11-25 Reset pulse added
2022-11-29 keyboard mode working
2022-12-03 Stop making noise upon startup
2022-12-04 Before fixing HW issues
2022-12-07 Analog redesign: - Power: Add voltage and current test points - MCU: use PA11/PA12 for USB DFU interface - MCU: add NRST reset switch - Slew: increase portamento cap - VCO: invert trim pots - VCF: le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
2023-01-07 Analog Redesign: - Power: Build ververse polarity protection using P-Mosfet and Zener Diode - (https://www.youtube.com/watch?v=Ltx4vovY5Z4 - 1:28) - Power: Build adjustable buck regulator for 8-9V st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
2023-01-08 Keep selected note always active for editing Fix annoying gate issue
2023-01-21 progress 2023-01-21
2023-01-21 DRC: no severe errors
2023-01-22 Stitching and decoupling vias added
2023-01-28 LCSC component looked up
2023-01-28 Add gerbers and bom
2023-01-29 Prepare for JLC order, manual correction tps63070
2023-01-29 Geographical reannotate
2023-01-29 Order placement 2023-01-29
2023-01-30 Modify toggle switches (footprint and 3D model) Align R value designators Add JLC component placement checkup file
2023-01-31 modify version variable
2023-01-31 Create new 0v3 folder
2023-01-31 purge fp-info-cache from git
2023-02-17 switch to KiCad 7
2023-02-20 adapt drivers to mcu connection reconfiguration
2023-02-26 Suppress new CMake warning on RWX segments Add 2nd demo option Flush pending gates on sequencer stop Improve keyboard performance mode Add chromatic quantization Reflect 0v2 RGB led mapping Impove UI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
2023-02-26 Start working on faceplate All holes for frontend components added
2023-02-28 Speaker grill ready Test knob spin silkscreen with KiCad tools
2023-03-01 Algorithmic Speaker Grill added
2023-03-02 Back to sequence when all buttons are released
2023-03-12 Faceplate 2023-03-12
2023-03-12 Add Liv greyscale
2023-03-13 Fix model name position Add F.Mask auto generation
2023-03-13 Retain silkscreen in front of foto with soldermask
2023-03-13 Add separators and SloBlo logos
2023-03-14 Remove B.Mask on Speaker Grill (darken backside)
2023-03-15 Add version tag on backside Add silkscreen space around switches
2023-03-25 Reduce EG cap to 4u7 Reduce LFO cap to 220n VCO R23: 470K, C13: 10n
2023-03-26 Update speaker footprint
2023-03-29 EG: raise Rf of comparator circuit to improve performance LFO: raise coupling resistor for higher amplitude, adapt cap for more musical ranges
2023-03-29 Add another LFO cap for easier modding please MCU connectors to the backside Relocate reset button KiCad 7.0.1
2023-03-30 Add License file
2023-03-30 Create LICENSE
2023-03-30 Increase loudness
2023-03-30 Apply loudness patch to 0v3
2023-03-30 Optimize input handling Blank default track fix quantization issue
2023-03-30 Enable key press duration measurement
2023-03-31 Shift all IO control to UiController
2023-03-31 Introduce different ui modes
2023-03-31 Add quantize util method
2023-03-31 make note length editable
2023-04-01 Add sequence edit options
2023-04-01 CubeMX 6.8.0
2023-04-02 Save model and restore on startup
2023-04-03 Definition of selected colour hues Use 16 bit flash sector for storage Improve first and last step UI
2023-04-03 Add github build and relase action
2023-04-03 Fix GCC version string for Github actions
2023-04-03 More fixes on github action
2023-04-03 GH action housekeeping
2023-04-03 Further constrain GH action
2023-04-03 ensure first step and last step won't commute Some notes how to trigger a new release
2023-04-07 ensure first step and last step won't commute move FlashStorage to segment 4 (FW size grown too big) Make sequence and clock pulse measure divisors editable Pulse selected step also if gate not enabl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
2023-04-08 build on version tag, only start changelog v0.2.2
2023-04-12 RV11 = 100K update BOM RV2 = 100K C13 = 10n R23 = 470K
2023-04-12 Normalize hardware file structure
2023-04-12 remove 0v3 subfolder
2023-04-12 add 0v2 status
2023-04-12 publish new hardware folder structure
2023-04-16 Backport from 0v3
2023-04-16 Update BOM with changes from 0v3
2023-04-16 Initial build instructions
2023-04-17 exxclude pre-assebled and not required components from BOM
2023-04-17 further build instructions
2023-04-17 exclude reset switch from BOM
2023-04-18 More build instructions
2023-04-19 add DFU flash mode to makefile
2023-04-22 Add firmare DFU flash procedure
2023-04-22 Remove 0v1 schematics Add 0v2 schematic pdf
2023-04-22 Commit changePattern using tune knob
2023-04-23 begin changelog 0.2.3
2023-05-02 Generate peripheral init code as .h/.c pairs
2023-06-06 Create MIDI/CDC USB Composite device
2023-06-08 Add Realtime Midi Handler function hook Add USBDBG routine (50 char max) Enable mulit-message MIDI data receive
2023-06-22 USB Midi Sync working
2023-06-22 Purge run mode concept
2023-06-22 turn off debug log Silence synth on slave stop Update USB product string
2023-06-24 Midi note output generation while playing
2023-06-25 make stm cube compile
2023-08-28 YT Links added
2023-09-14 Rename Decay -> Release
2023-12-28 Upgrade to MxCube 6.10.0
2024-12-29 Fix slave mode sync issue Upgrade to MxCube Version 6.13.0 and STM32Cube 1.28.1 Release v0.2.4
2024-12-29 Fix packet size committed to Receive method
2024-12-29 Apply cosmetics to USB product string
2024-12-30 Add ohmyposh terminal font
2024-12-30 Play incoming midi notes in idle mode working
2025-01-04 Incoming midi play in idle mode Store last note to selected step
2025-04-08 Add line coding properties according to Phil's Lab video
